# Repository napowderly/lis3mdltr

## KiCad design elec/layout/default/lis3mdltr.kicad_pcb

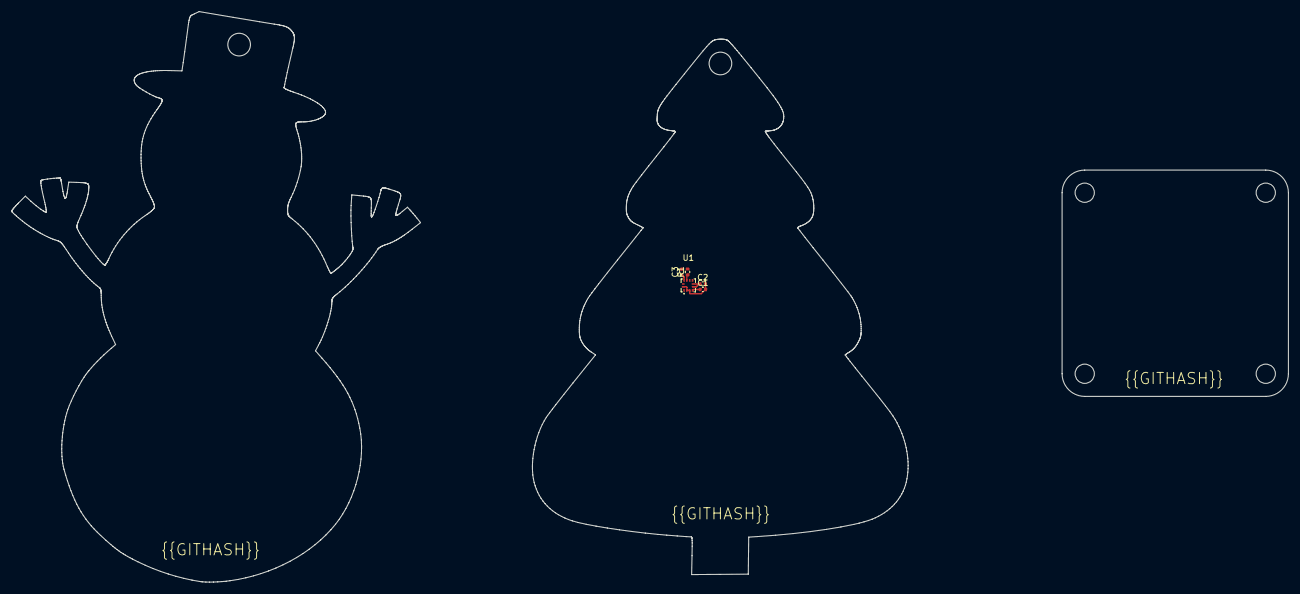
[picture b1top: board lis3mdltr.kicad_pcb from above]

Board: 2 copper layers, 66.4 x 94.6 mm, 5 parts (0 on the bottom side), 4 nets.

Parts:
C1, C3: 16V 100nF X7R ±10% 0402 Multilayer Ceramic Capaci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; C0402
C2: 25V 1uF X5R ±10% 0402 Multilayer Ceramic Capacito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; C0402
R1: 62.5mW Thick Film Resistors ±100ppm/℃ ±1% 1kΩ 040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; R0402
U1: LGA-12_L2.0-W2.0-P0.50-BL

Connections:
c1: C1.1, U1.4
gnd: C1.2, C2.2, C3.2, R1.2, U1.2, U1.3, U1.12
miso: R1.1, U1.9
vcc: C2.1, C3.1, U1.5, U1.6, U1.10

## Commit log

2024-02-17 Configure project
2024-02-17 initial layout
2024-02-17 layout update
2024-03-08 updating layout
